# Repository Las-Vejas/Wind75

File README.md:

# Wind75
A 75% keyboard.

This keyboard is composed of 68 switches, 1 Nice!nano2, a battery ill rip out from a power bank and a gpio pin expander.

I made this keyboard because ive been begging my mom to bring a keyboard back from her work and she keeps forgetting. And honestly id rather have a custom mechanical keyboard rather than a crusty office keyboard.

# Everything below is deprecated as i have to remodel the whole entire thing as i forgot mounting holes (YAY) so reroute in progress.

## CAD
Made in fusion360.

## PCB

Lowk my best pcb so far.

## Schematic

## Firmware

I am using KMK, currently very basic.

## BOM
| **Name**              | **Quantity** | **Price** | **Link**                                                                                                                                                                                                                                                                                                                                                                                                                                                                                                                                                                                                   |
| --------------------- | ------------ | --------- | ---------------------------------------------------------------------------------------------------------------------------------------------------------------------------------------------------------------------------------------------------------------------------------------------------------------------------------------------------------------------------------------------------------------------------------------------------------------------------------------------------------------------------------------------------------------------------------------------------------- |
| Gateron G Pro 3.0 Red | 70           | $22.26    | [ali](https://www.aliexpress.com/item/1005005746164310.html?spm=a2g0o.detail.0.0.1f0dSQcRSQcR3J&productId=1005005746164310&pdp_ext_f=%7B%22tabScene%22%3A%22retail%22%2C%22sku_id%22%3A12000034197538289%2C%22origProductId%22%3A%221005005746164310%22%7D&)                                                                                                                                                                                                                                                                                                                                               |
| M2 screws             | 4            | $2.36     | [ali](https://www.aliexpress.com/item/1005006384784732.html?spm=a2g0o.productlist.main.1.5c4971f1vZs1Td&algo_pvid=4befbcdb-aa3b-4fb4-833e-fe46e1ba2c55&algo_exp_id=4befbcdb-aa3b-4fb4-833e-fe46e1ba2c55-0&pdp_ext_f=%7B%22order%22%3A%2228%22%2C%22eval%22%3A%221%22%7D&pdp_npi=4%40dis%21USD%211.20%210.99%21%21%211.20%210.99%21%402141131717522615031892241ed7ac%2112000036978193523%21sea%21LT%216401819456%21ABX&curPageLogUid=7HFUJm4J5Z60&utparam-url=scene%3Asearch%7Cquery_from%3A)                                                                                                               |
| M2 Heatsets           | 4            | $4.03     | [ali](https://www.aliexpress.com/item/1005006838108683.html?spm=a2g0o.productlist.main.1.2c0bjDACjDAC7e&aem_p4p_detail=20250711122420609381794867400000858735&algo_pvid=11d9e40a-cf46-4f94-b4ff-13c2af7a9f69&algo_exp_id=11d9e40a-cf46-4f94-b4ff-13c2af7a9f69-0&pdp_ext_f=%7B%22order%22%3A%22247%22%2C%22eval%22%3A%221%22%7D&pdp_npi=4%40dis%21USD%214.03%210.99%21%21%214.03%210.99%21%40213ba0c517522618599565234e0aba%2112000038467725083%21sea%21LT%216401819456%21ABX&curPageLogUid=XOPE5RnGGsKW&utparam-url=scene%3Asearch%7Cquery_from%3A&search_p4p_id=20250711122420609381794867400000858735_1) |
| Diodes                | 68           | $1.38     | [ali](https://www.aliexpress.com/item/4000142272546.html?spm=a2g0o.productlist.main.6.3ecf5562RC4vuY&algo_pvid=f2600214-28b8-4632-b422-754c4bc524a1&algo_exp_id=f2600214-28b8-4632-b422-754c4bc524a1-5&pdp_ext_f=%7B%22order%22%3A%221591%22%2C%22eval%22%3A%221%22%7D&pdp_npi=4%40dis%21USD%211.38%210.99%21%21%219.85%217.07%21%40213ba8cc17522515802381389e121c%2110000000428321629%21sea%21LT%216401819456%21ABX&curPageLogUid=FnfMaQmXCEAQ&utparam-url=scene%3Asearch%7Cquery_from%3A)                                                                                                                |
| Nice Nano dupe        | 1            | $10.65    | [ali](https://www.aliexpress.com/item/1005009003677135.html?spm=a2g0o.productlist.main.6.4ec72c1cu8PDFE&algo_pvid=40c64990-4f09-4df0-97db-7269f21bc034&algo_exp_id=40c64990-4f09-4df0-97db-7269f21bc034-5&pdp_ext_f=%7B%22order%22%3A%224%22%2C%22eval%22%3A%221%22%7D&pdp_npi=4%40dis%21USD%2122.19%2110.65%21%21%21158.41%2176.04%21%40213ba0c517522511900168751e0aa3%2112000047536102285%21sea%21LT%216401819456%21ABX&curPageLogUid=XS4WURIloebY&utparam-url=scene%3Asearch%7Cquery_from%3A)                                                                                                           |
| MCP23017_SP           | 1            | $5.38     | [ali](https://www.aliexpress.com/item/1005008066849865.html?spm=a2g0o.productlist.main.1.ab74115c6dOQMz&algo_pvid=4cc48396-1822-4573-a8a4-94b192b8e4f9&algo_exp_id=4cc48396-1822-4573-a8a4-94b192b8e4f9-0&pdp_ext_f=%7B%22order%22%3A%22154%22%2C%22eval%22%3A%221%22%7D&pdp_npi=4%40dis%21USD%213.00%210.99%21%21%213.00%210.99%21%400b1bf20817522491014751504e77bc%2112000043519110514%21sea%21LT%216401819456%21ABX&curPageLogUid=RR561RSyNIcg&utparam-url=scene%3Asearch%7Cquery_from%3A)                                                                                                              |
| Hot swap sockets      | 68           | $10.01    | [ali](https://www.aliexpress.com/item/1005008954571807.html?spm=a2g0o.productlist.main.17.7ca8777ddpQBY3&algo_pvid=7d831310-3855-4dd3-a4c6-0bbc6b7c0b72&algo_exp_id=7d831310-3855-4dd3-a4c6-0bbc6b7c0b72-16&pdp_ext_f=%7B%22order%22%3A%2274%22%2C%22eval%22%3A%221%22%7D&pdp_npi=4%40dis%21USD%214.26%210.99%21%21%2130.40%217.06%21%402101246417522513678455630ef01c%2112000047352129246%21sea%21LT%216401819456%21ABX&curPageLogUid=veWb9xhPkuZB&utparam-url=scene%3Asearch%7Cquery_from%3A)                                                                                                            |
| PCB                   | 5            | $16.33    | N/A 
| Keycaps               | 1            | $22.62    | [ali](https://www.aliexpress.com/item/1005008049516517.html?spm=a2g0o.productlist.main.7.10b069546DFMLj&algo_pvid=804c14ec-0d8e-4f0b-bc79-14bdb5ce7ff8&algo_exp_id=804c14ec-0d8e-4f0b-bc79-14bdb5ce7ff8-6&pdp_ext_f=%7B%22order%22%3A%22110%22%2C%22eval%22%3A%221%22%7D&pdp_npi=6%40dis%21EUR%2116.55%2110.82%21%21%21135.18%2188.41%21%40211b81a317553510837492085e8c96%2112000043433491718%21sea%21LT%210%21ABX%211%210%21m03_new_user%3A-29895%3Bn_tag%3A-29910%3BpisId%3A5000000174211184&curPageLogUid=oB5lUzq4KaoT&utparam-url=scene%3Asearch%7Cquery_from%3A%7Cx_object_id%3A1005008049516517%7C_p_origin_prod%3A)
|                       | TOTAL        | $95,02 | |

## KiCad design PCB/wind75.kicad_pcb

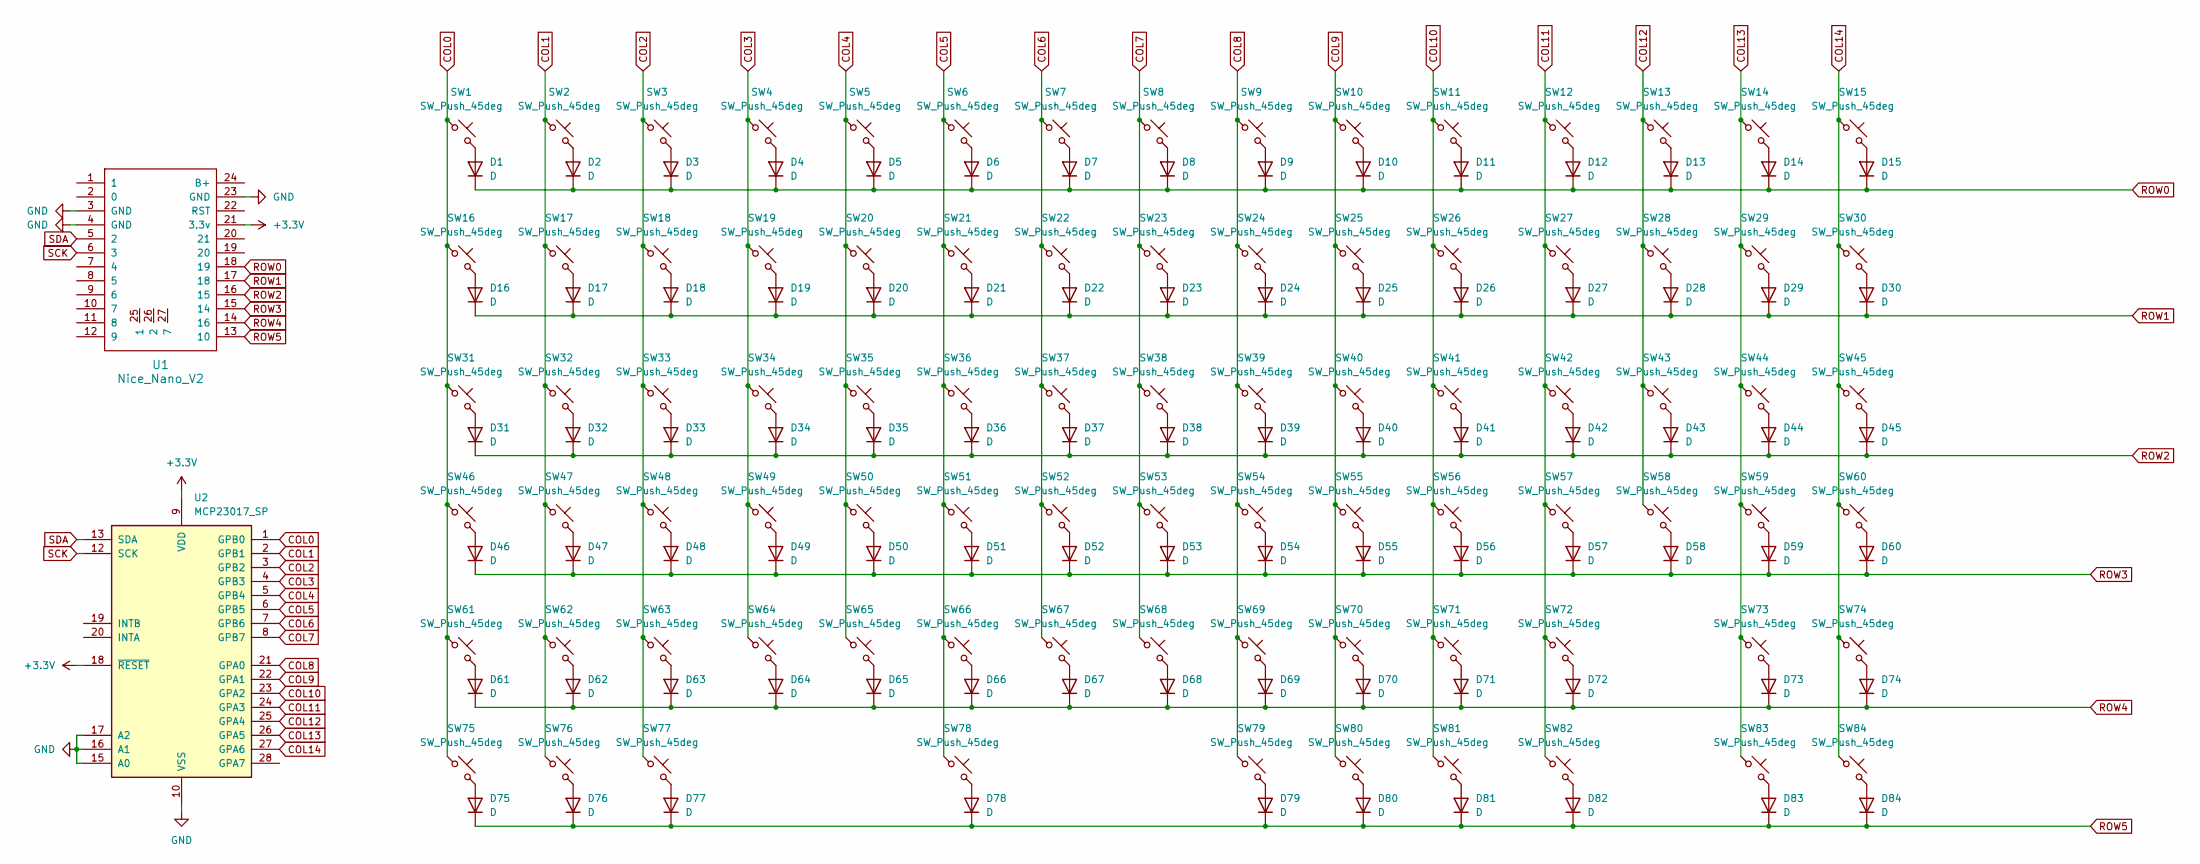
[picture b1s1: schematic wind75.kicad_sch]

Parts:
D1, D2, D3, D4, D5, D6, D7, D8, D9, D10, D11, D12, D13, D14, D15, D16, D17, D18, D19, D20, D21, D22, D23, D24, D25, D26, D27, D28, D29, D30, D31, D32, D33, D34, D35, D36, D37, D38, D39, D40, D41, D42, D43, D44, D45, D46, D47, D48, D49, D50, D51, D52, D53, D54, D55, D56, D57, D58, D59, D60, D61, D62, D63, D64, D65, D66, D67, D68, D69, D70, D71, D72, D73, D74, D75, D76, D77, D78, D79, D80, D81, D82, D83, D84: D; Diode_SOD-123
SW1, SW2, SW3, SW4, SW5, SW6, SW7, SW8, SW9, SW10, SW11, SW12, SW13, SW14, SW15, SW16, SW17, SW18, SW19, SW20, SW21, SW22, SW23, SW24, SW25, SW26, SW27, SW28, SW29, SW31, SW33, SW34, SW35, SW36, SW37, SW38, SW39, SW40, SW41, SW42, SW43, SW44, SW46, SW48, SW49, SW50, SW51, SW52, SW53, SW54, SW55, SW56, SW57, SW58, SW60, SW62, SW63, SW64, SW65, SW66, SW67, SW68, SW69, SW70, SW71, SW73, SW74, SW79, SW80, SW81, SW82, SW83, SW84: SW_Push_45deg; Hotswap_MX_1.00u
SW30: SW_Push_45deg; Hotswap_MX_2.00u
SW32, SW45: SW_Push_45deg; Hotswap_MX_1.50u
SW47, SW72: SW_Push_45deg; Hotswap_MX_1.75u
SW59, SW61: SW_Push_45deg; Hotswap_MX_2.25u
SW75, SW76, SW77: SW_Push_45deg; Hotswap_MX_1.25u
SW78: SW_Push_45deg; Hotswap_MX_6.25u
U1: Nice_Nano_V2
U2: MCP23017_SP; DIP-28_W7.62mm

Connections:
+3.3V: U1.21 (3.3v), U2.9 (VDD), U2.18 (~RESET)
COL0: SW1.1, SW16.1, SW31.1, SW46.1, SW61.1, SW75.1, U2.1 (GPB0)
COL1: SW2.1, SW17.1, SW32.1, SW47.1, SW62.1, SW76.1, U2.2 (GPB1)
COL2: SW3.1, SW18.1, SW33.1, SW48.1, SW63.1, SW77.1, U2.3 (GPB2)
COL3: SW4.1, SW19.1, SW34.1, SW49.1, SW64.1, U2.4 (GPB3)
COL4: SW5.1, SW20.1, SW35.1, SW50.1, SW65.1, U2.5 (GPB4)
COL5: SW6.1, SW21.1, SW36.1, SW51.1, SW66.1, SW78.1, U2.6 (GPB5)
COL6: SW7.1, SW22.1, SW37.1, SW52.1, SW67.1, U2.7 (GPB6)
COL7: SW8.1, SW23.1, SW38.1, SW53.1, SW68.1, U2.8 (GPB7)
COL8: SW9.1, SW24.1, SW39.1, SW54.1, SW69.1, SW79.1, U2.21 (GPA0)
COL9: SW10.1, SW25.1, SW40.1, SW55.1, SW70.1, SW80.1, U2.22 (GPA1)
COL10: SW11.1, SW26.1, SW41.1, SW56.1, SW71.1, SW81.1, U2.23 (GPA2)
COL11: SW12.1, SW27.1, SW42.1, SW57.1, SW72.1, SW82.1, U2.24 (GPA3)
COL12: SW13.1, SW28.1, SW43.1, SW58.1, U2.25 (GPA4)
COL13: SW14.1, SW29.1, SW44.1, SW59.1, SW73.1, SW83.1, U2.26 (GPA5)
COL14: SW15.1, SW30.1, SW45.1, SW60.1, SW74.1, SW84.1, U2.27 (GPA6)
GND: U1.3 (GND), U1.4 (GND), U1.23 (GND), U2.10 (VSS), U2.15 (A0), U2.16 (A1), U2.17 (A2)
unnamed: D1.2 (A), SW1.2
unnamed: D2.2 (A), SW2.2
unnamed: D3.2 (A), SW3.2
unnamed: D4.2 (A), SW4.2
unnamed: D5.2 (A), SW5.2
unnamed: D6.2 (A), SW6.2
unnamed: D7.2 (A), SW7.2
unnamed: D8.2 (A), SW8.2
unnamed: D9.2 (A), SW9.2
unnamed: D10.2 (A), SW10.2
unnamed: D11.2 (A), SW11.2
unnamed: D12.2 (A), SW12.2
unnamed: D13.2 (A), SW13.2
unnamed: D14.2 (A), SW14.2
unnamed: D15.2 (A), SW15.2
unnamed: D16.2 (A), SW16.2
unnamed: D17.2 (A), SW17.2
unnamed: D18.2 (A), SW18.2
unnamed: D19.2 (A), SW19.2
unnamed: D20.2 (A), SW20.2
unnamed: D21.2 (A), SW21.2
unnamed: D22.2 (A), SW22.2
unnamed: D23.2 (A), SW23.2
unnamed: D24.2 (A), SW24.2
unnamed: D25.2 (A), SW25.2
unnamed: D26.2 (A), SW26.2
unnamed: D27.2 (A), SW27.2
unnamed: D28.2 (A), SW28.2
unnamed: D29.2 (A), SW29.2
unnamed: D30.2 (A), SW30.2
unnamed: D31.2 (A), SW31.2
unnamed: D32.2 (A), SW32.2
unnamed: D33.2 (A), SW33.2
unnamed: D34.2 (A), SW34.2
unnamed: D35.2 (A), SW35.2
unnamed: D36.2 (A), SW36.2
unnamed: D37.2 (A), SW37.2
unnamed: D38.2 (A), SW38.2
unnamed: D39.2 (A), SW39.2
unnamed: D40.2 (A), SW40.2
unnamed: D41.2 (A), SW41.2
unnamed: D42.2 (A), SW42.2
unnamed: D43.2 (A), SW43.2
unnamed: D44.2 (A), SW44.2
unnamed: D45.2 (A), SW45.2
unnamed: D46.2 (A), SW46.2
unnamed: D47.2 (A), SW47.2
unnamed: D48.2 (A), SW48.2
unnamed: D49.2 (A), SW49.2
unnamed: D50.2 (A), SW50.2
unnamed: D51.2 (A), SW51.2
unnamed: D52.2 (A), SW52.2
unnamed: D53.2 (A), SW53.2
unnamed: D54.2 (A), SW54.2
unnamed: D55.2 (A), SW55.2
unnamed: D56.2 (A), SW56.2
unnamed: D57.2 (A), SW57.2
unnamed: D58.2 (A), SW58.2
unnamed: D59.2 (A), SW59.2
unnamed: D60.2 (A), SW60.2
unnamed: D61.2 (A), SW61.2
unnamed: D62.2 (A), SW62.2
unnamed: D63.2 (A), SW63.2
unnamed: D64.2 (A), SW64.2
unnamed: D65.2 (A), SW65.2
unnamed: D66.2 (A), SW66.2
unnamed: D67.2 (A), SW67.2
unnamed: D68.2 (A), SW68.2
unnamed: D69.2 (A), SW69.2
unnamed: D70.2 (A), SW70.2
unnamed: D71.2 (A), SW71.2
unnamed: D72.2 (A), SW72.2
unnamed: D73.2 (A), SW73.2
unnamed: D74.2 (A), SW74.2
unnamed: D75.2 (A), SW75.2
unnamed: D76.2 (A), SW76.2
unnamed: D77.2 (A), SW77.2
unnamed: D78.2 (A), SW78.2
unnamed: D79.2 (A), SW79.2
unnamed: D80.2 (A), SW80.2
unnamed: D81.2 (A), SW81.2
unnamed: D82.2 (A), SW82.2
unnamed: D83.2 (A), SW83.2
unnamed: D84.2 (A), SW84.2
ROW0: D1.1 (K), D2.1 (K), D3.1 (K), D4.1 (K), D5.1 (K), D6.1 (K), D7.1 (K), D8.1 (K), D9.1 (K), D10.1 (K), D11.1 (K), D12.1 (K), D13.1 (K), D14.1 (K), D15.1 (K), U1.18 (19)
ROW1: D16.1 (K), D17.1 (K), D18.1 (K), D19.1 (K), D20.1 (K), D21.1 (K), D22.1 (K), D23.1 (K), D24.1 (K), D25.1 (K), D26.1 (K), D27.1 (K), D28.1 (K), D29.1 (K), D30.1 (K), U1.17 (18)
ROW2: D31.1 (K), D32.1 (K), D33.1 (K), D34.1 (K), D35.1 (K), D36.1 (K), D37.1 (K), D38.1 (K), D39.1 (K), D40.1 (K), D41.1 (K), D42.1 (K), D43.1 (K), D44.1 (K), D45.1 (K), U1.16 (15)
ROW3: D46.1 (K), D47.1 (K), D48.1 (K), D49.1 (K), D50.1 (K), D51.1 (K), D52.1 (K), D53.1 (K), D54.1 (K), D55.1 (K), D56.1 (K), D57.1 (K), D58.1 (K), D59.1 (K), D60.1 (K), U1.15 (14)
ROW4: D61.1 (K), D62.1 (K), D63.1 (K), D64.1 (K), D65.1 (K), D66.1 (K), D67.1 (K), D68.1 (K), D69.1 (K), D70.1 (K), D71.1 (K), D72.1 (K), D73.1 (K), D74.1 (K), U1.14 (16)
ROW5: D75.1 (K), D76.1 (K), D77.1 (K), D78.1 (K), D79.1 (K), D80.1 (K), D81.1 (K), D82.1 (K), D83.1 (K), D84.1 (K), U1.13 (10)
SCK: U1.6 (3), U2.12 (SCK)
SDA: U1.5 (2), U2.13 (SDA)

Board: 2 copper layers, 170 parts (84 on the bottom side), 109 nets, no tracks yet.

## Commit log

2025-07-11 A LOT of work
2025-07-11 add image
2025-07-11 added silkscreen
2025-07-16 added silk screen
2025-07-29 Rename atsisiųsti.png to Images/atsisiųsti.png
2025-07-29 3d files
2025-07-29 Rename Wind75 Assembled v1.step to CAD/Wind75 Assembled v1.step
2025-07-29 step
2025-07-29 Rename Wind75 Assembled v3.step to CAD/Wind75 Assembled v3.step
2025-07-29 Rename Wind75 Assembled v2 parts - Wind75 top v3.stl to Production/Wind75 Assembled v2 parts - Wind75 top v3.stl
2025-08-16 Update README.md to add keycaps
2025-08-16 add csv
2025-08-16 Update JOURNAL.md change 1
2025-08-17 Update JOURNAL.md added images of keeb and wrote more
2025-09-13 review (not finished)
2025-11-05 Update README with deprecation notice
    Added a note about deprecation and remodeling due to forgotten mounting holes.
